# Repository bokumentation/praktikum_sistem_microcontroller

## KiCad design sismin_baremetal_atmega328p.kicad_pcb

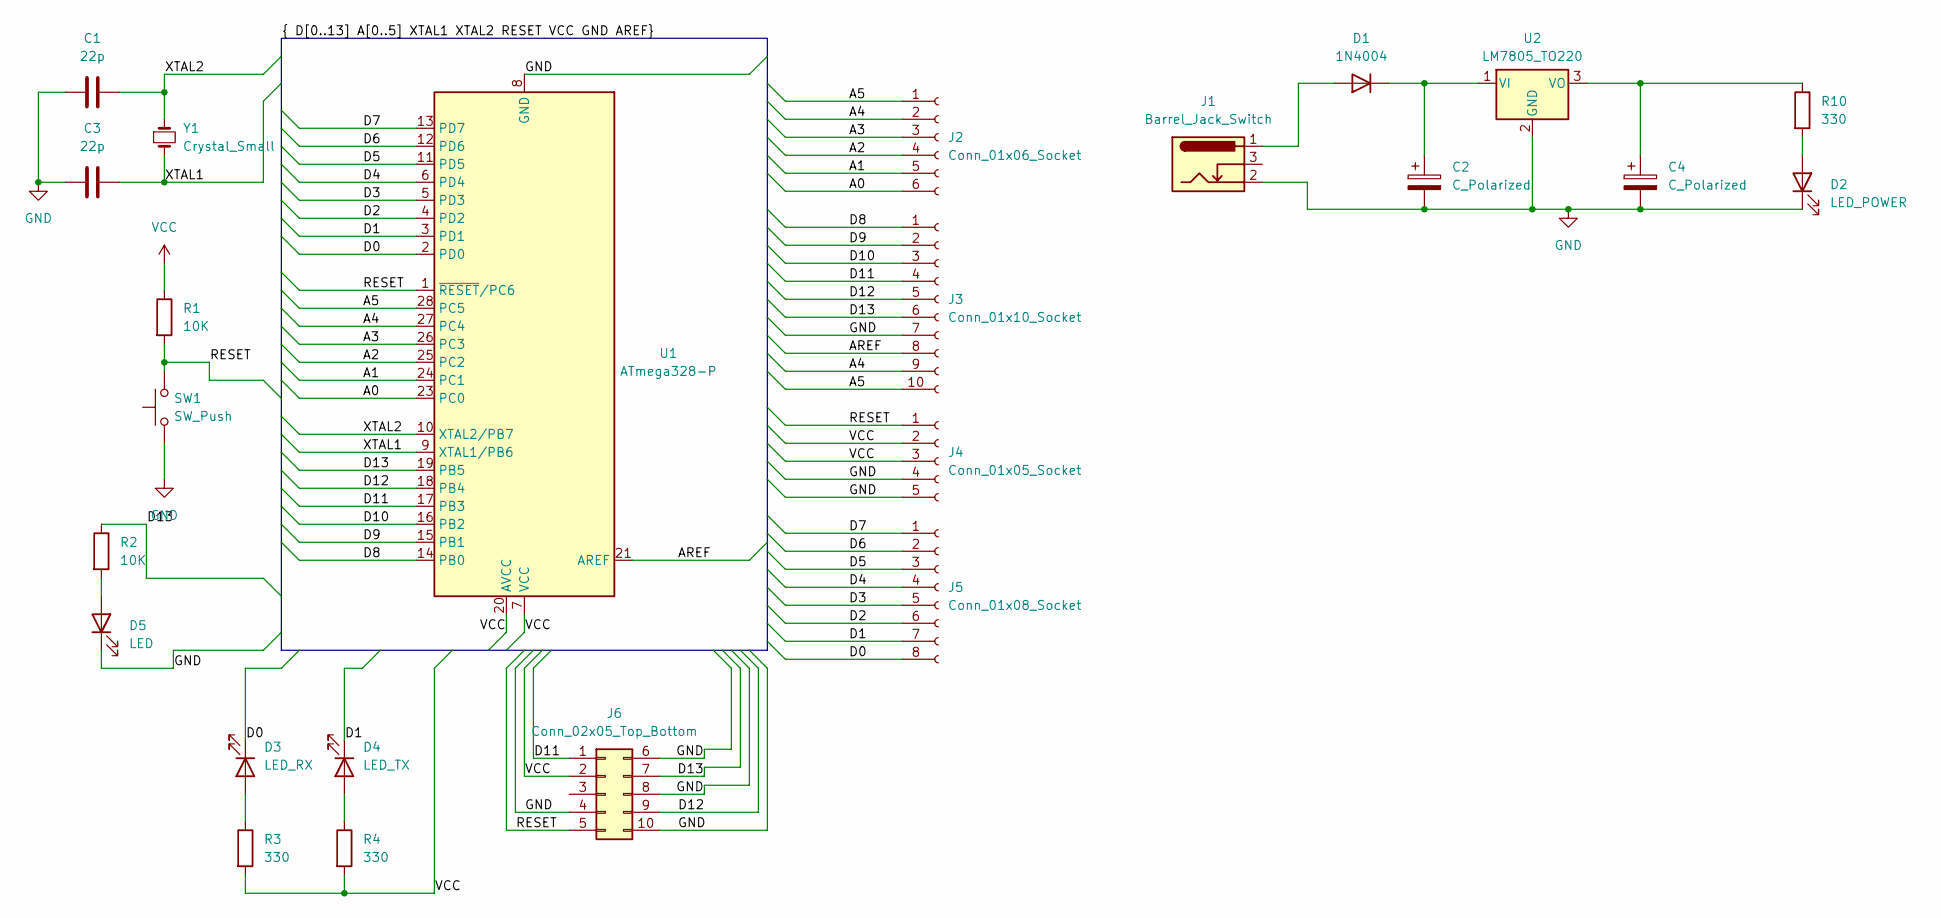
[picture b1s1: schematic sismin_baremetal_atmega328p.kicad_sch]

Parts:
C1, C3: 22p; C_Disc_D3.0mm_W1.6mm_P2.50mm
C2, C4: C_Polarized; CP_Radial_D5.0mm_P2.50mm
D1: 1N4004; D_DO-41_SOD81_P7.62mm_Horizontal
D2: LED_POWER; LED_D5.0mm
D3: LED_RX; LED_D5.0mm
D4: LED_TX; LED_D5.0mm
D5: LED; LED_D5.0mm
J1: Barrel_Jack_Switch; BarrelJack_Horizontal
J2: Conn_01x06_Socket; PinSocket_1x06_P2.54mm_Vertical
J3: Conn_01x10_Socket; PinSocket_1x10_P2.54mm_Vertical
J4: Conn_01x05_Socket; PinSocket_1x05_P2.54mm_Vertical
J5: Conn_01x08_Socket; PinSocket_1x08_P2.54mm_Vertical
J6: Conn_02x05_Top_Bottom; IDC-Header_2x05_P2.54mm_Vertical
R1, R2: 10K; R_Axial_DIN0207_L6.3mm_D2.5mm_P7.62mm_Horizontal
R3, R4, R10: 330; R_Axial_DIN0207_L6.3mm_D2.5mm_P7.62mm_Horizontal
SW1: SW_Push; SW_PUSH_6mm_H4.3mm
U1: ATmega328-P; DIP-28_W7.62mm
U2: LM7805_TO220; TO-220-3_Horizontal_TabDown
Y1: Crystal_Small; Crystal_HC49-4H_Vertical

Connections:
/A0: J2.6, U1.23 (PC0)
/A1: J2.5, U1.24 (PC1)
/A2: J2.4, U1.25 (PC2)
/A3: J2.3, U1.26 (PC3)
/A4: J2.2, J3.9, U1.27 (PC4)
/A5: J2.1, J3.10, U1.28 (PC5)
/AREF: J3.8, U1.21 (AREF)
/D0: D3.1 (K), J5.8, U1.2 (PD0)
/D1: D4.1 (K), J5.7, U1.3 (PD1)
/D2: J5.6, U1.4 (PD2)
/D3: J5.5, U1.5 (PD3)
/D4: J5.4, U1.6 (PD4)
/D5: J5.3, U1.11 (PD5)
/D6: J5.2, U1.12 (PD6)
/D7: J5.1, U1.13 (PD7)
/D8: J3.1, U1.14 (PB0)
/D9: J3.2, U1.15 (PB1)
/D10: J3.3, U1.16 (PB2)
/D11: J3.4, J6.1, U1.17 (PB3)
/D12: J3.5, J6.9, U1.18 (PB4)
/D13: J3.6, J6.7, R2.1, U1.19 (PB5)
/RESET: J4.1, J6.5, R1.2, SW1.2, U1.1 (~RESET/PC6)
/XTAL1: C3.1, U1.9 (XTAL1/PB6), Y1.2
/XTAL2: C1.1, U1.10 (XTAL2/PB7), Y1.1
GND: C1.2, C2.2, C3.2, C4.2, D2.1 (K), D5.1 (K), J1.2, J3.7, J4.4, J4.5, J6.4, J6.6, J6.8, J6.10, SW1.1, U1.8 (GND), U1.22 (GND), U2.2 (GND)
unnamed: D1.2 (A), J1.1
unnamed: C2.1, D1.1 (K), U2.1 (VI)
unnamed: D2.2 (A), R10.2
unnamed: D3.2 (A), R3.1
unnamed: D4.2 (A), R4.1
unnamed: D5.2 (A), R2.2
unnamed: C4.1, R10.1, U2.3 (VO)
VCC: J4.2, J4.3, J6.2, R1.1, R3.2, R4.2, U1.7 (VCC), U1.20 (AVCC)

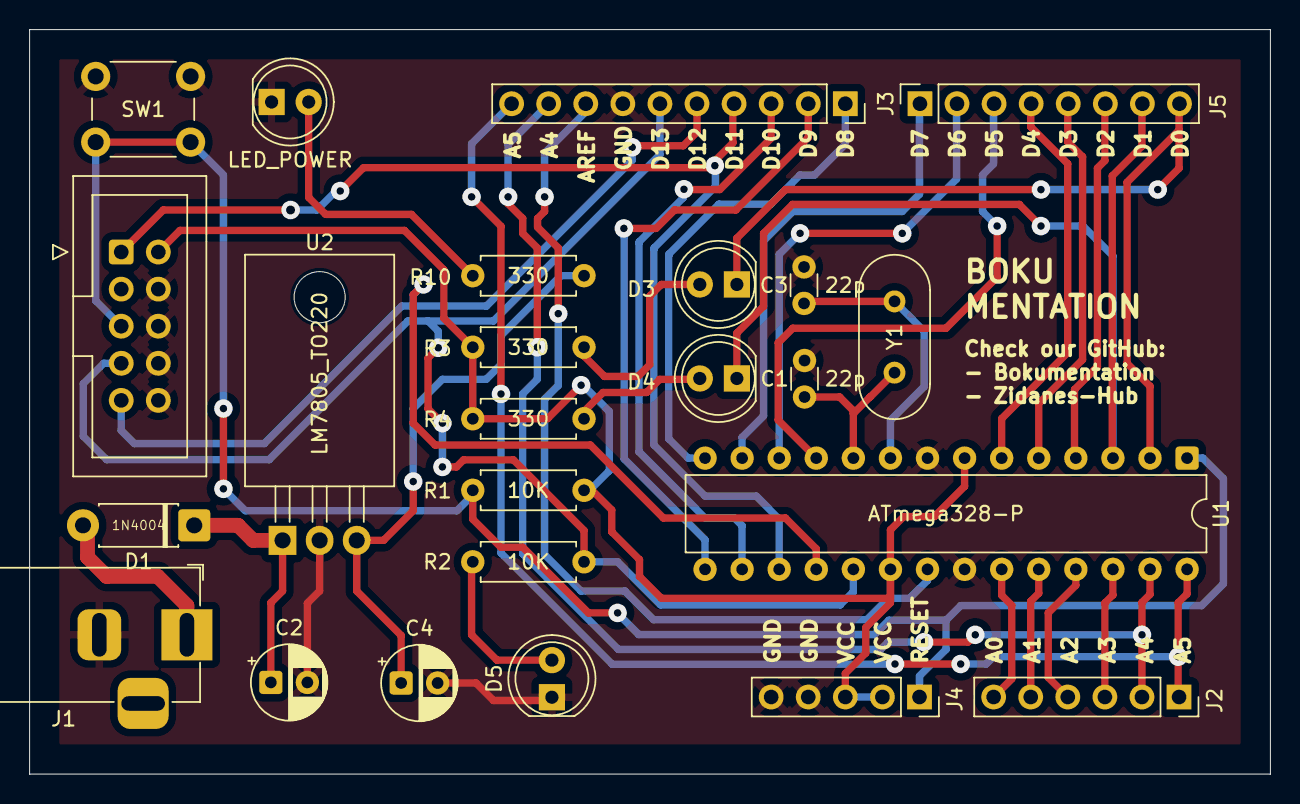
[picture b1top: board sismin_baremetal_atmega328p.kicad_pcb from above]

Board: 2 copper layers, 85.0 x 51.0 mm, 24 parts (0 on the bottom side), 33 nets.

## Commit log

2025-10-02 git init
2025-10-09 update 241009
2025-10-14 update 251013
2025-10-16 update 251016
2025-10-16 update night
